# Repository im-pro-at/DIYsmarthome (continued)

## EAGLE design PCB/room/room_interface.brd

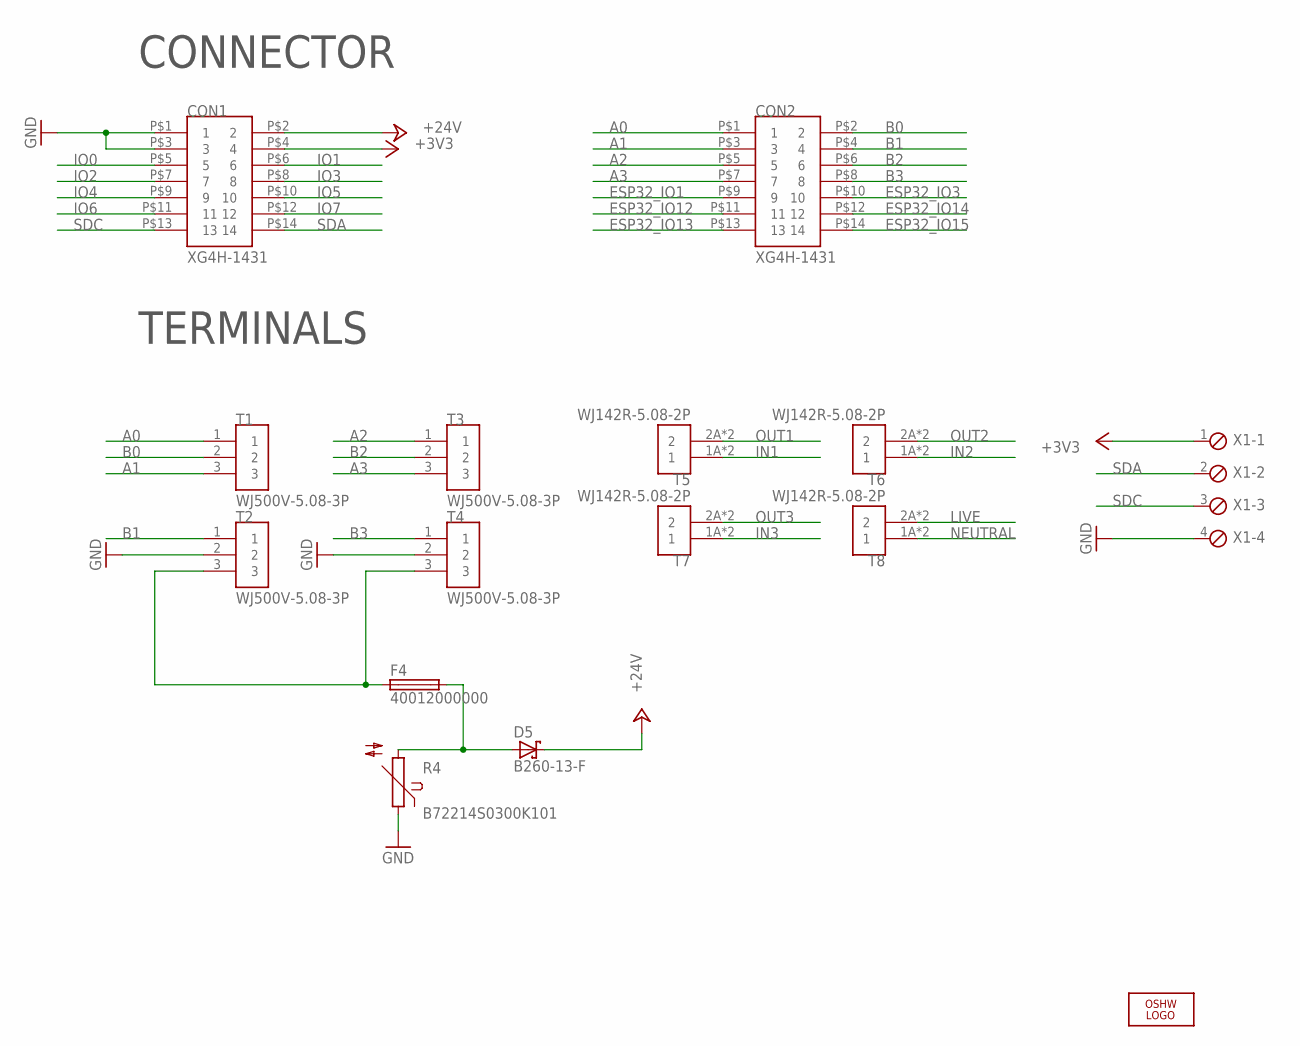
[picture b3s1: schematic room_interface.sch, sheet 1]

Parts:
CON1, CON2: XG4H-1431
D5: B260-13-F; SMB
F4: 40012000000; 400
LOGO1: OSHW_LOGO_FILLX0350-NT; OSHW_FILLX350_NOTEXT
R4: B72214S0300K101; S14K300
T1, T2, T3, T4: WJ500V-5.08-3P
T5, T6, T7, T8: WJ142R-5.08-2P; WJ142R.5.08-2P
X1: MPT4; 4POL254

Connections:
+3V3: CON1.P$4 (4), X1.1; also elsewhere on the board
+24V: CON1.P$2 (2), D5.C; also elsewhere on the board
A0: CON2.P$1 (1), T1.1
A1: CON2.P$3 (3), T1.3
A2: CON2.P$5 (5), T3.1
A3: CON2.P$7 (7), T3.3
B0: CON2.P$2 (2), T1.2
B1: CON2.P$4 (4), T2.1
B2: CON2.P$6 (6), T3.2
B3: CON2.P$8 (8), T4.1
ESP32_IO1: CON2.P$9 (9)
ESP32_IO3: CON2.P$10 (10)
ESP32_IO12: CON2.P$11 (11)
ESP32_IO13: CON2.P$13 (13)
ESP32_IO14: CON2.P$12 (12)
ESP32_IO15: CON2.P$14 (14)
GND: CON1.P$1 (1), CON1.P$3 (3), R4.1, T2.2, T4.2, X1.4; also elsewhere on the board
IN1: T5.1A (1), T5.1B (1); also elsewhere on the board
IN2: T6.1A (1), T6.1B (1); also elsewhere on the board
IN3: T7.1A (1), T7.1B (1); also elsewhere on the board
IO0: CON1.P$5 (5); also elsewhere on the board
IO1: CON1.P$6 (6); also elsewhere on the board
IO2: CON1.P$7 (7); also elsewhere on the board
IO3: CON1.P$8 (8)
IO4: CON1.P$9 (9)
IO5: CON1.P$10 (10); also elsewhere on the board
IO6: CON1.P$11 (11); also elsewhere on the board
IO7: CON1.P$12 (12); also elsewhere on the board
LIVE: T8.2A (2), T8.2B (2); also elsewhere on the board
unnamed: D5.A, F4.P$2 (2), R4.2
unnamed: F4.P$1 (1), T2.3, T4.3
NEUTRAL: T8.1A (1), T8.1B (1); also elsewhere on the board
OUT1: T5.2A (2), T5.2B (2); also elsewhere on the board
OUT2: T6.2A (2), T6.2B (2); also elsewhere on the board
OUT3: T7.2A (2), T7.2B (2); also elsewhere on the board
SDA: CON1.P$14 (14), X1.2
SDC: CON1.P$13 (13), X1.3

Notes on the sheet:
CONNECTOR
TERMINALS

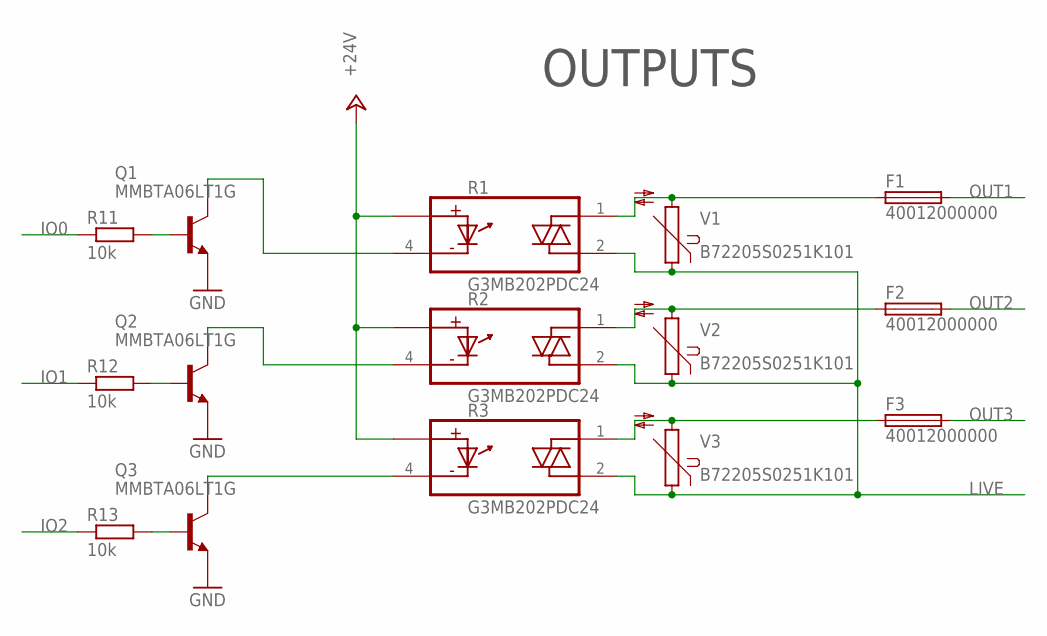
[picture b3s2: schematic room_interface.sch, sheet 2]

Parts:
F1, F2, F3: 40012000000; 400
Q1, Q2, Q3: MMBTA06LT1G; SOT23-BEC
R1, R2, R3: G3MB202PDC24; RELAY_G3MB202PDC12
R11, R12, R13: 10k; R1206
V1, V2, V3: B72205S0251K101; S05K250

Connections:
+24V: R1.3 (IN+), R2.3 (IN+), R3.3 (IN+); also elsewhere on the board
GND: Q1.E, Q2.E, Q3.E; also elsewhere on the board
IO0: R11.1; also elsewhere on the board
IO1: R12.1; also elsewhere on the board
IO2: R13.1; also elsewhere on the board
LIVE: R1.2 (OUT2), R2.2 (OUT2), R3.2 (OUT2), V1.1, V2.1, V3.1; also elsewhere on the board
unnamed: F1.P$1 (1), R1.1 (OUT1), V1.2
unnamed: F2.P$1 (1), R2.1 (OUT1), V2.2
unnamed: F3.P$1 (1), R3.1 (OUT1), V3.2
unnamed: Q1.B, R11.2
unnamed: Q1.C, R1.4 (IN-)
unnamed: Q2.B, R12.2
unnamed: Q2.C, R2.4 (IN-)
unnamed: Q3.B, R13.2
unnamed: Q3.C, R3.4 (IN-)
OUT1: F1.P$2 (2); also elsewhere on the board
OUT2: F2.P$2 (2); also elsewhere on the board
OUT3: F3.P$2 (2); also elsewhere on the board

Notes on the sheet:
OUTPUTS

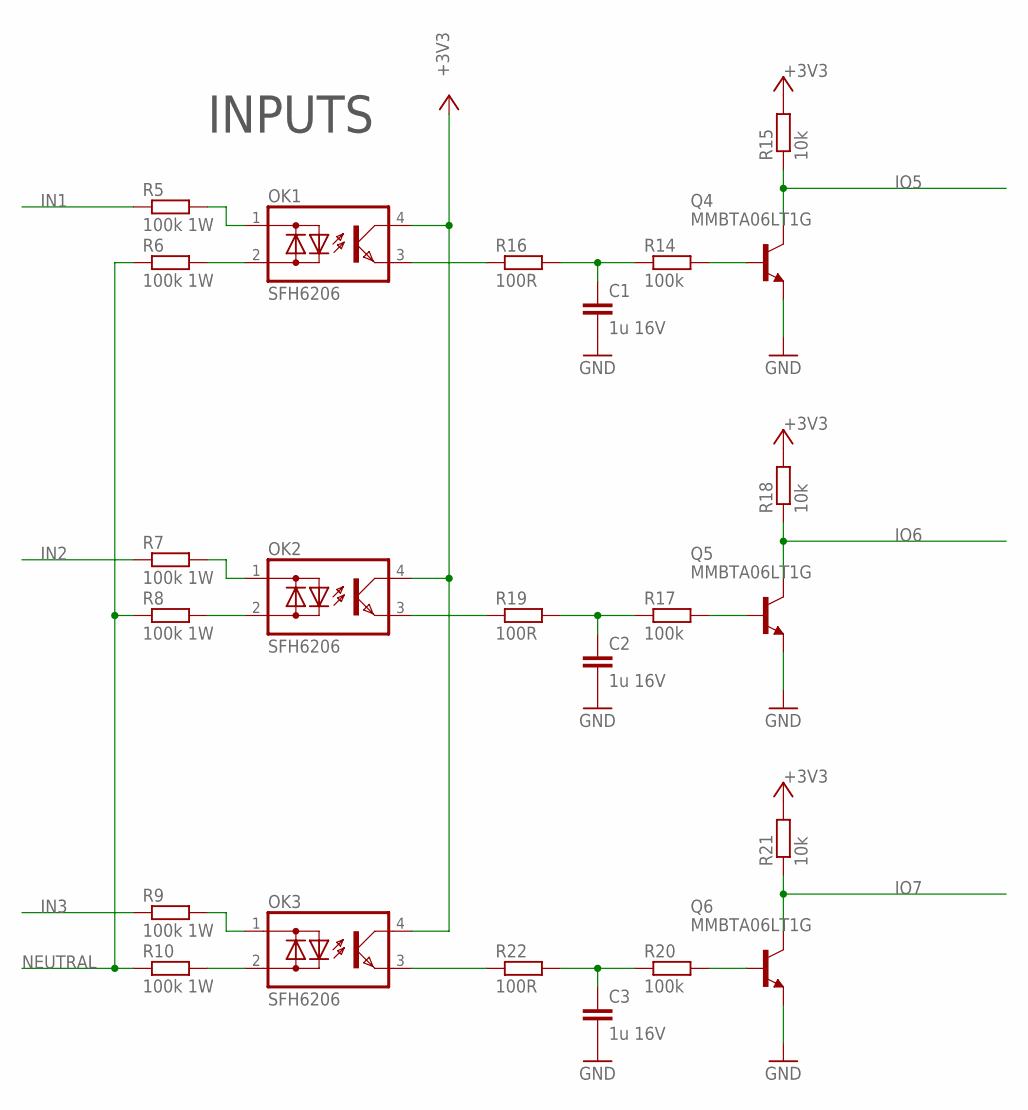
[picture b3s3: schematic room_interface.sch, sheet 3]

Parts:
C1, C2, C3: 1u 16V; C0805
OK1, OK2, OK3: SFH6206; DIL4-SMD
Q4, Q5, Q6: MMBTA06LT1G; SOT23-BEC
R5, R6, R7, R8, R9, R10: 100k 1W; R2010
R14, R17, R20: 100k; R1206
R15, R18, R21: 10k; R1206
R16, R19, R22: 100R; R1206

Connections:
+3V3: OK1.4 (C), OK2.4 (C), OK3.4 (C), R15.2, R18.2, R21.2; also elsewhere on the board
GND: C1.2, C2.2, C3.2, Q4.E, Q5.E, Q6.E; also elsewhere on the board
IN1: R5.1; also elsewhere on the board
IN2: R7.1; also elsewhere on the board
IN3: R9.1; also elsewhere on the board
IO5: Q4.C, R15.1; also elsewhere on the board
IO6: Q5.C, R18.1; also elsewhere on the board
IO7: Q6.C, R21.1; also elsewhere on the board
unnamed: OK1.2 (AC2), R6.2
unnamed: OK1.1 (AC1), R5.2
unnamed: OK2.1 (AC1), R7.2
unnamed: OK2.2 (AC2), R8.2
unnamed: OK3.1 (AC1), R9.2
unnamed: OK3.2 (AC2), R10.2
unnamed: Q4.B, R14.2
unnamed: OK1.3 (E), R16.1
unnamed: C1.1, R14.1, R16.2
unnamed: Q5.B, R17.2
unnamed: OK2.3 (E), R19.1
unnamed: C2.1, R17.1, R19.2
unnamed: Q6.B, R20.2
unnamed: OK3.3 (E), R22.1
unnamed: C3.1, R20.1, R22.2
NEUTRAL: R6.1, R8.1, R10.1; also elsewhere on the board

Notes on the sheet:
INPUTS

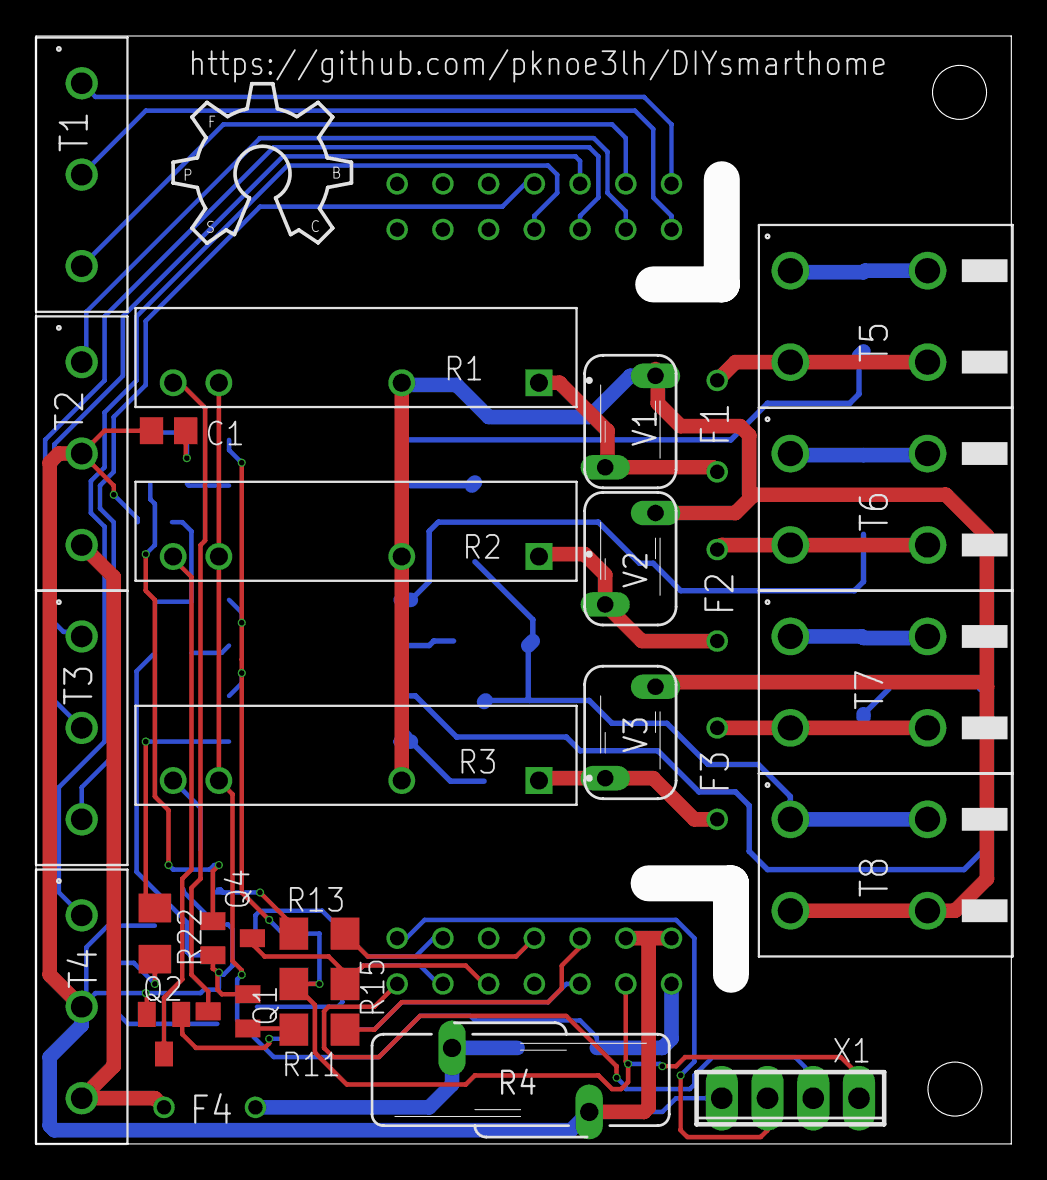
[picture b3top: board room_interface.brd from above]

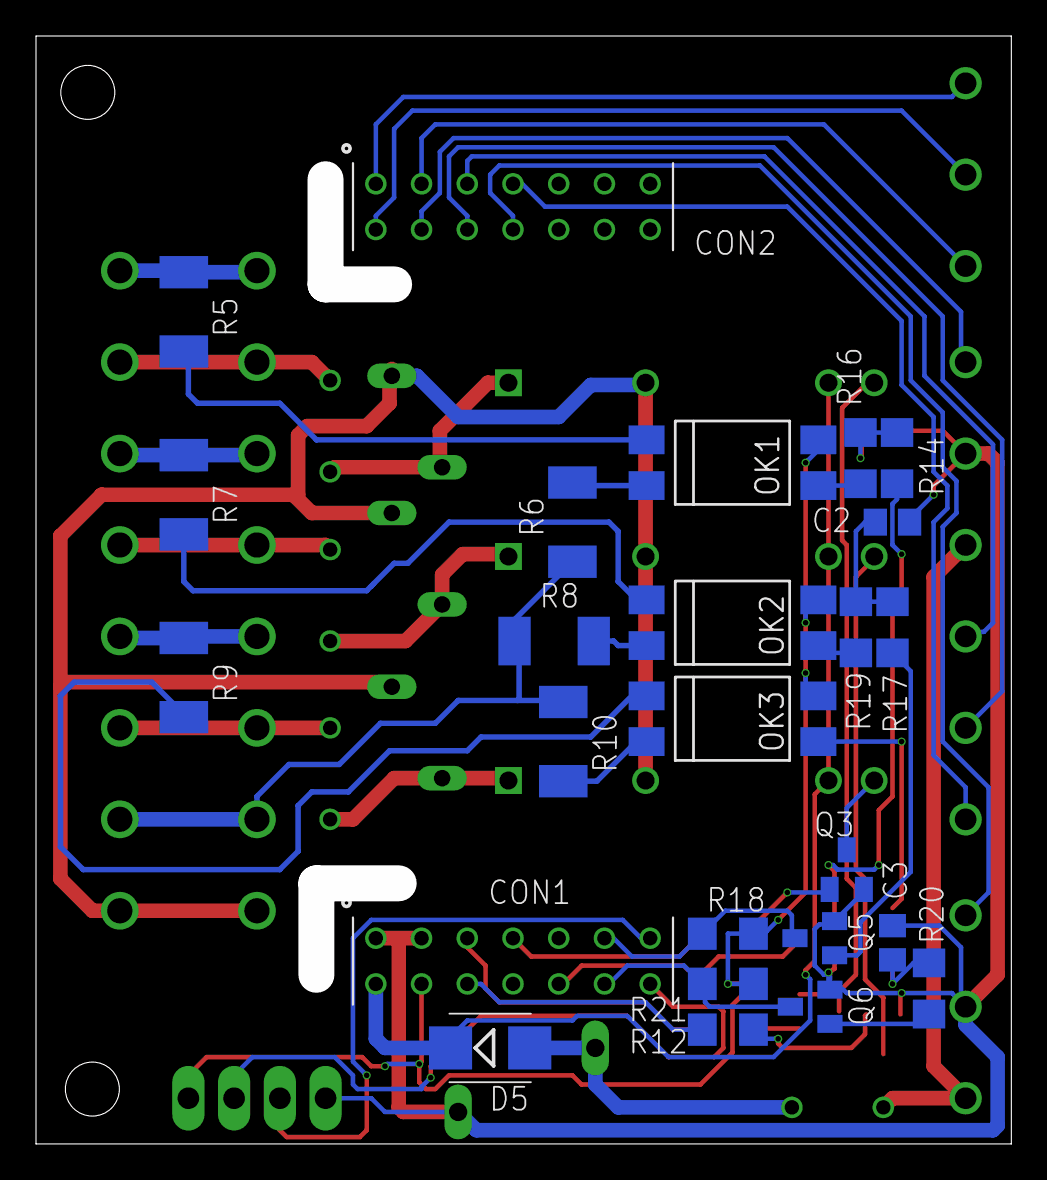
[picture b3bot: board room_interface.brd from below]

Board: 2 copper layers, 54.2 x 61.6 mm, 54 parts (25 on the bottom side), 53 nets.

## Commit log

2019-04-17 start of PCB desigen
2019-04-19 first version of schematic ready
2019-04-19 Placement done
2019-04-21 finished routing for room sensor PCB
2019-04-22 finished interface PCB
2019-04-23 finished PCB designs
2019-04-26 PCB ordered
